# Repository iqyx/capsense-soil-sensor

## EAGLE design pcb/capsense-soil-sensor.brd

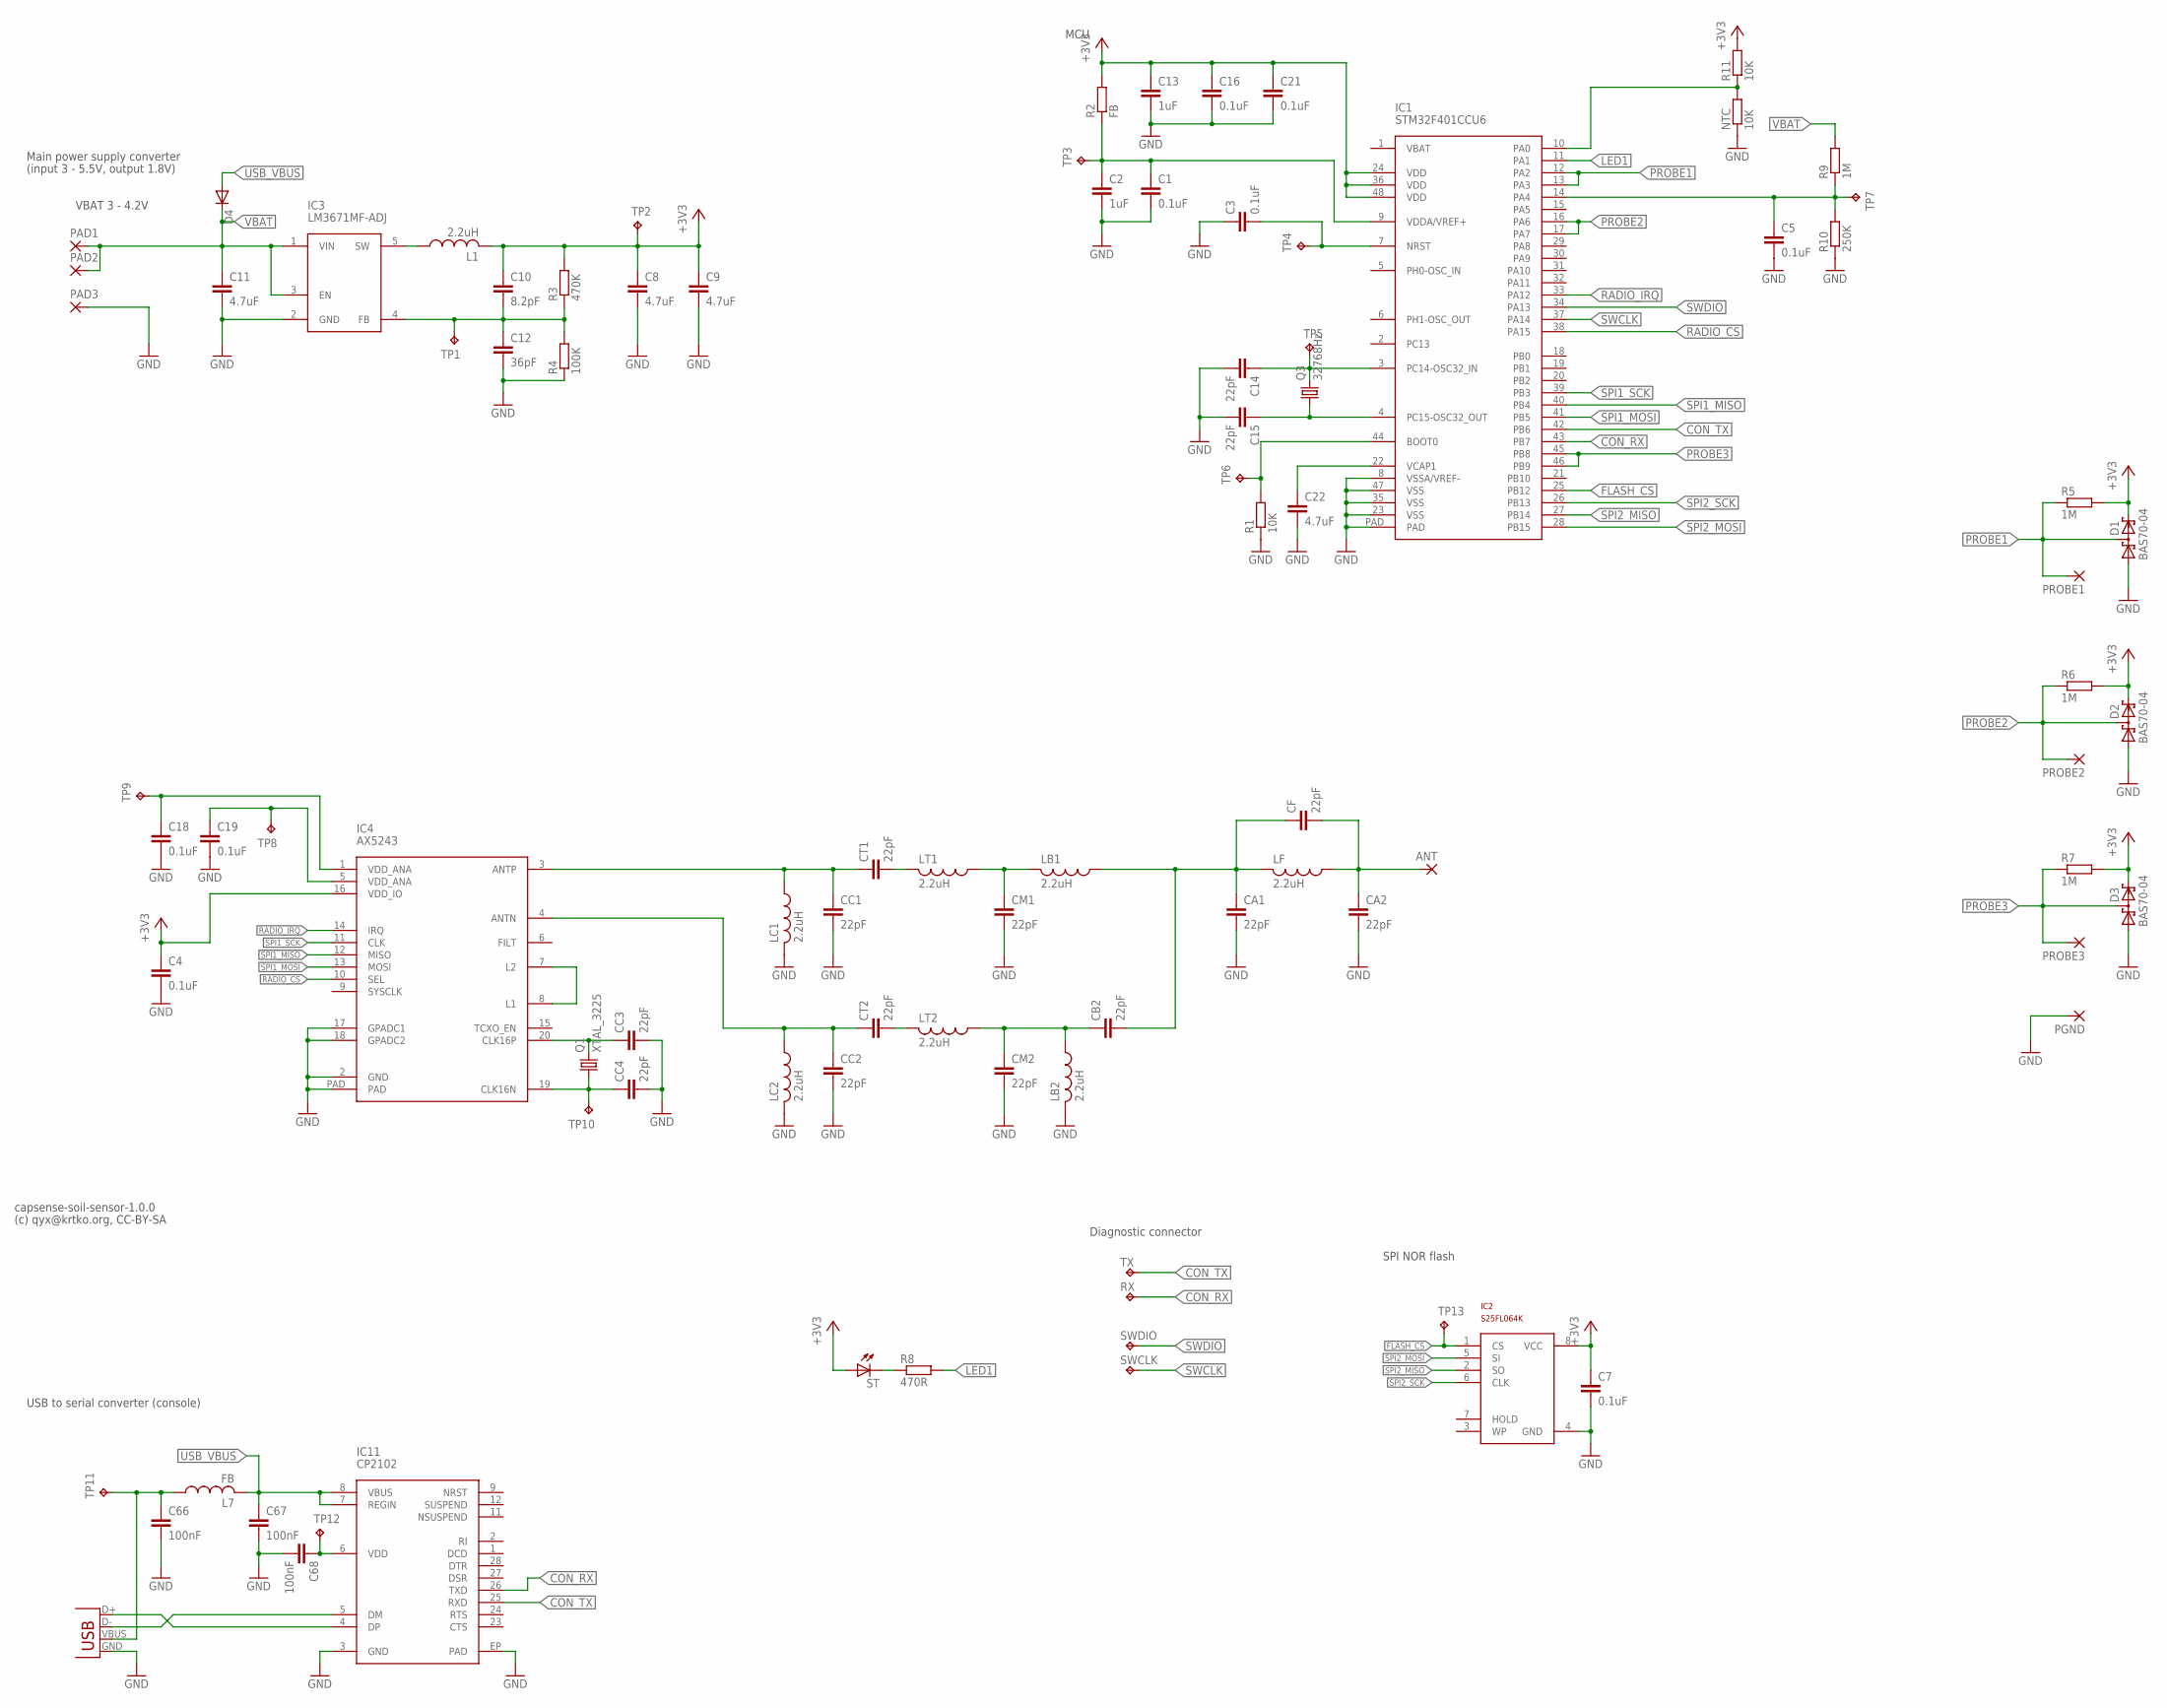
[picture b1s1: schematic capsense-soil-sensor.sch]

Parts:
ANT: 2,15/1,0
C1, C3, C4, C5, C7, C16, C18, C19, C21: 0.1uF; C0603
C2, C13: 1uF; C0603
C8, C9, C11: 4.7uF; C0805
C10: 8.2pF; C0603
C12: 36pF; C0603
C14, C15: 22pF; C0603
C22: 4.7uF; C0603
C66, C67, C68: 100nF; C0603
CA1, CA2: 22pF; C0603
CB2: 22pF; C0603
CC1, CC2, CC3, CC4: 22pF; C0603
CF: 22pF; C0603
CM1, CM2: 22pF; C0603
CT1, CT2: 22pF; C0603
D1, D2, D3: BAS70-04; SOT23
D4: DIODE-SOD110-R; SOD110-R
IC1: STM32F401CCU6; UFQFPN48
IC2: S25FL064K; SO-08M
IC3: LM3671MF-ADJ; SOT23-5
IC4: AX5243; QFN20
IC11: CP2102; QFN28
L1: 2.2uH; L2825P
L7: FB; L2012C
LB1, LB2: 2.2uH; L2012C
LC1, LC2: 2.2uH; L2012C
LF: 2.2uH; L2012C
LT1, LT2: 2.2uH; L2012C
NTC: 10K; R0603
PAD1, PAD2: SMD5; SMD2,54-5,08
PAD3: 2,15/1,0
PGND: 2,15/1,0
PROBE1, PROBE2, PROBE3: 2,15/1,0
Q1: XTAL_3225
Q3: 32768Hz; TC26H
R1, R11: 10K; R0603
R2: FB; R0603
R3: 470K; R0603
R4: 100K; R0603
R5, R6, R7, R9: 1M; R0603
R8: 470R; R0603
R10: 250K; R0603
RX: TPB2,54; B2,54
ST: LEDCHIPLED_0603; CHIPLED_0603
SWCLK: TPB2,54; B2,54
SWDIO: TPB2,54; B2,54
TP1, TP2, TP3, TP4, TP5, TP6, TP7, TP8, TP9, TP10, TP11, TP12, TP13: TPB1,27; B1,27
TX: TPB2,54; B2,54
X5: USB-MICROB

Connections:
+3V3: C4.1, C7.1, C8.1, C9.1, C10.1, C13.1, C16.1, C21.1, D1.2 (C2), D2.2 (C2), D3.2 (C2), IC1.24 (VDD), IC1.36 (VDD), IC1.48 (VDD), IC2.8 (VCC), IC4.16 (VDD_IO), L1.2, R2.2, R3.2, R5.2, R6.2, R7.2, R11.2, ST.A, TP2.TP
CON_RX: IC1.43 (PB7), IC11.26 (TXD), RX.TP
CON_TX: IC1.42 (PB6), IC11.25 (RXD), TX.TP
FLASH_CS: IC1.25 (PB12), IC2.1 (CS), TP13.TP
GND: C1.2, C2.2, C3.1, C4.2, C5.2, C7.2, C8.2, C9.2, C11.2, C12.2, C13.2, C14.2, C15.2, C16.2, C18.2, C19.2, C21.2, C22.2, C66.2, C67.2, C68.2, CA1.2, CA2.2, CC1.2, CC2.2, CC3.2, CC4.2, CM1.2, CM2.2, D1.1 (A1), D2.1 (A1), D3.1 (A1), IC1.8 (VSSA/VREF-), IC1.23 (VSS), IC1.35 (VSS), IC1.47 (VSS), IC1.PAD, IC2.4 (GND), IC3.2 (GND), IC4.2 (GND), IC4.17 (GPADC1), IC4.18 (GPADC2), IC4.PAD, IC11.3 (GND), IC11.EP (PAD), LB2.2, LC1.2, LC2.2, NTC.1, PAD3.1, PGND.1, R1.1, R4.1, R10.1, X5.GND
LED1: IC1.11 (PA1), R8.2
unnamed: IC1.44 (BOOT0), R1.2, TP6.TP
unnamed: C1.1, C2.1, IC1.9 (VDDA/VREF+), R2.1, TP3.TP
unnamed: IC3.5 (SW), L1.1
unnamed: CC3.1, IC4.20 (CLK16P), Q1.3 (2)
unnamed: C22.1, IC1.22 (VCAP1)
unnamed: C3.2, IC1.7 (NRST), TP4.TP
unnamed: C10.2, C12.1, IC3.4 (FB), R3.1, R4.2, TP1.TP
unnamed: C5.1, IC1.14 (PA4), R9.1, R10.2, TP7.TP
unnamed: IC1.10 (PA0), NTC.2, R11.1
unnamed: CC1.1, CT1.1, IC4.3 (ANTP), LC1.1
unnamed: CC2.1, CT2.1, IC4.4 (ANTN), LC2.1
unnamed: IC4.7 (L2), IC4.8 (L1)
unnamed: CA1.1, CB2.2, CF.1, LB1.1, LF.2
unnamed: ANT.1, CA2.1, CF.2, LF.1
unnamed: CT1.2, LT1.2
unnamed: CM1.1, LB1.2, LT1.1
unnamed: CT2.2, LT2.2
unnamed: CB2.1, CM2.1, LB2.1, LT2.1
unnamed: C18.1, IC4.1 (VDD_ANA), TP9.TP
unnamed: CC4.1, IC4.19 (CLK16N), Q1.1, TP10.TP
unnamed: C14.1, IC1.3 (PC14-OSC32_IN), Q3.2, TP5.TP
unnamed: C19.1, IC4.5 (VDD_ANA), TP8.TP
unnamed: R8.1, ST.C
unnamed: C15.1, IC1.4 (PC15-OSC32_OUT), Q3.1
unnamed: IC11.4 (DP), X5.D+
unnamed: IC11.5 (DM), X5.D-
unnamed: C66.1, L7.1, TP11.TP, X5.VBUS
unnamed: C68.1, IC11.6 (VDD), TP12.TP
PROBE1: D1.3 (C1A2), IC1.12 (PA2), IC1.13 (PA3), PROBE1.1, R5.1
PROBE2: D2.3 (C1A2), IC1.16 (PA6), IC1.17 (PA7), PROBE2.1, R6.1
PROBE3: D3.3 (C1A2), IC1.45 (PB8), IC1.46 (PB9), PROBE3.1, R7.1
RADIO_CS: IC1.38 (PA15), IC4.10 (SEL)
RADIO_IRQ: IC1.33 (PA12), IC4.14 (IRQ)
SPI1_MISO: IC1.40 (PB4), IC4.12 (MISO)
SPI1_MOSI: IC1.41 (PB5), IC4.13 (MOSI)
SPI1_SCK: IC1.39 (PB3), IC4.11 (CLK)
SPI2_MISO: IC1.27 (PB14), IC2.2 (SO)
SPI2_MOSI: IC1.28 (PB15), IC2.5 (SI)
SPI2_SCK: IC1.26 (PB13), IC2.6 (CLK)
SWCLK: IC1.37 (PA14), SWCLK.TP
SWDIO: IC1.34 (PA13), SWDIO.TP
USB_VBUS: C67.1, D4.A, IC11.7 (REGIN), IC11.8 (VBUS), L7.2
VBAT: C11.1, D4.C, IC3.1 (VIN), IC3.3 (EN), PAD1.1, PAD2.1, R9.2

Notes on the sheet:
VBAT 3 - 4.2V
Main power supply converter
(input 3 - 5.5V, output 1.8V)
SPI NOR flash
MCU
Diagnostic connector
(c) qyx@krtko.org, CC-BY-SA
USB to serial converter (console)
capsense-soil-sensor-1.0.0

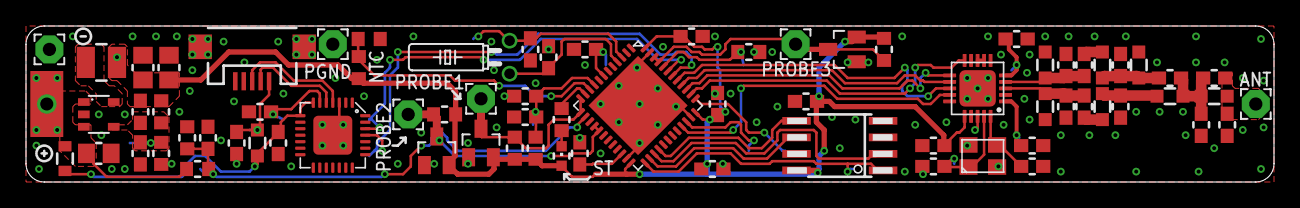
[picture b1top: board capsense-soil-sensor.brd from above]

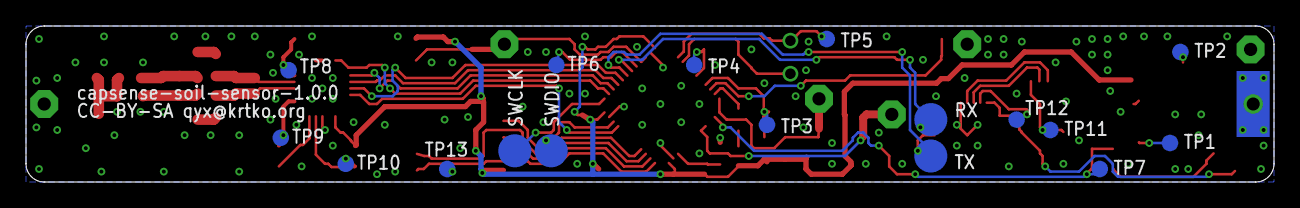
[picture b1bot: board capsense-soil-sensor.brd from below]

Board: 2 copper layers, 96.0 x 12.0 mm, 93 parts (18 on the bottom side), 49 nets.

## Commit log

2017-03-19 Create schematic and board layout
2017-03-19 Add Gerber data for seeedstudio fusion service

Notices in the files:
pcb/capsense-soil-sensor.brd:
CC-BY-SA qyx@krtko.org
